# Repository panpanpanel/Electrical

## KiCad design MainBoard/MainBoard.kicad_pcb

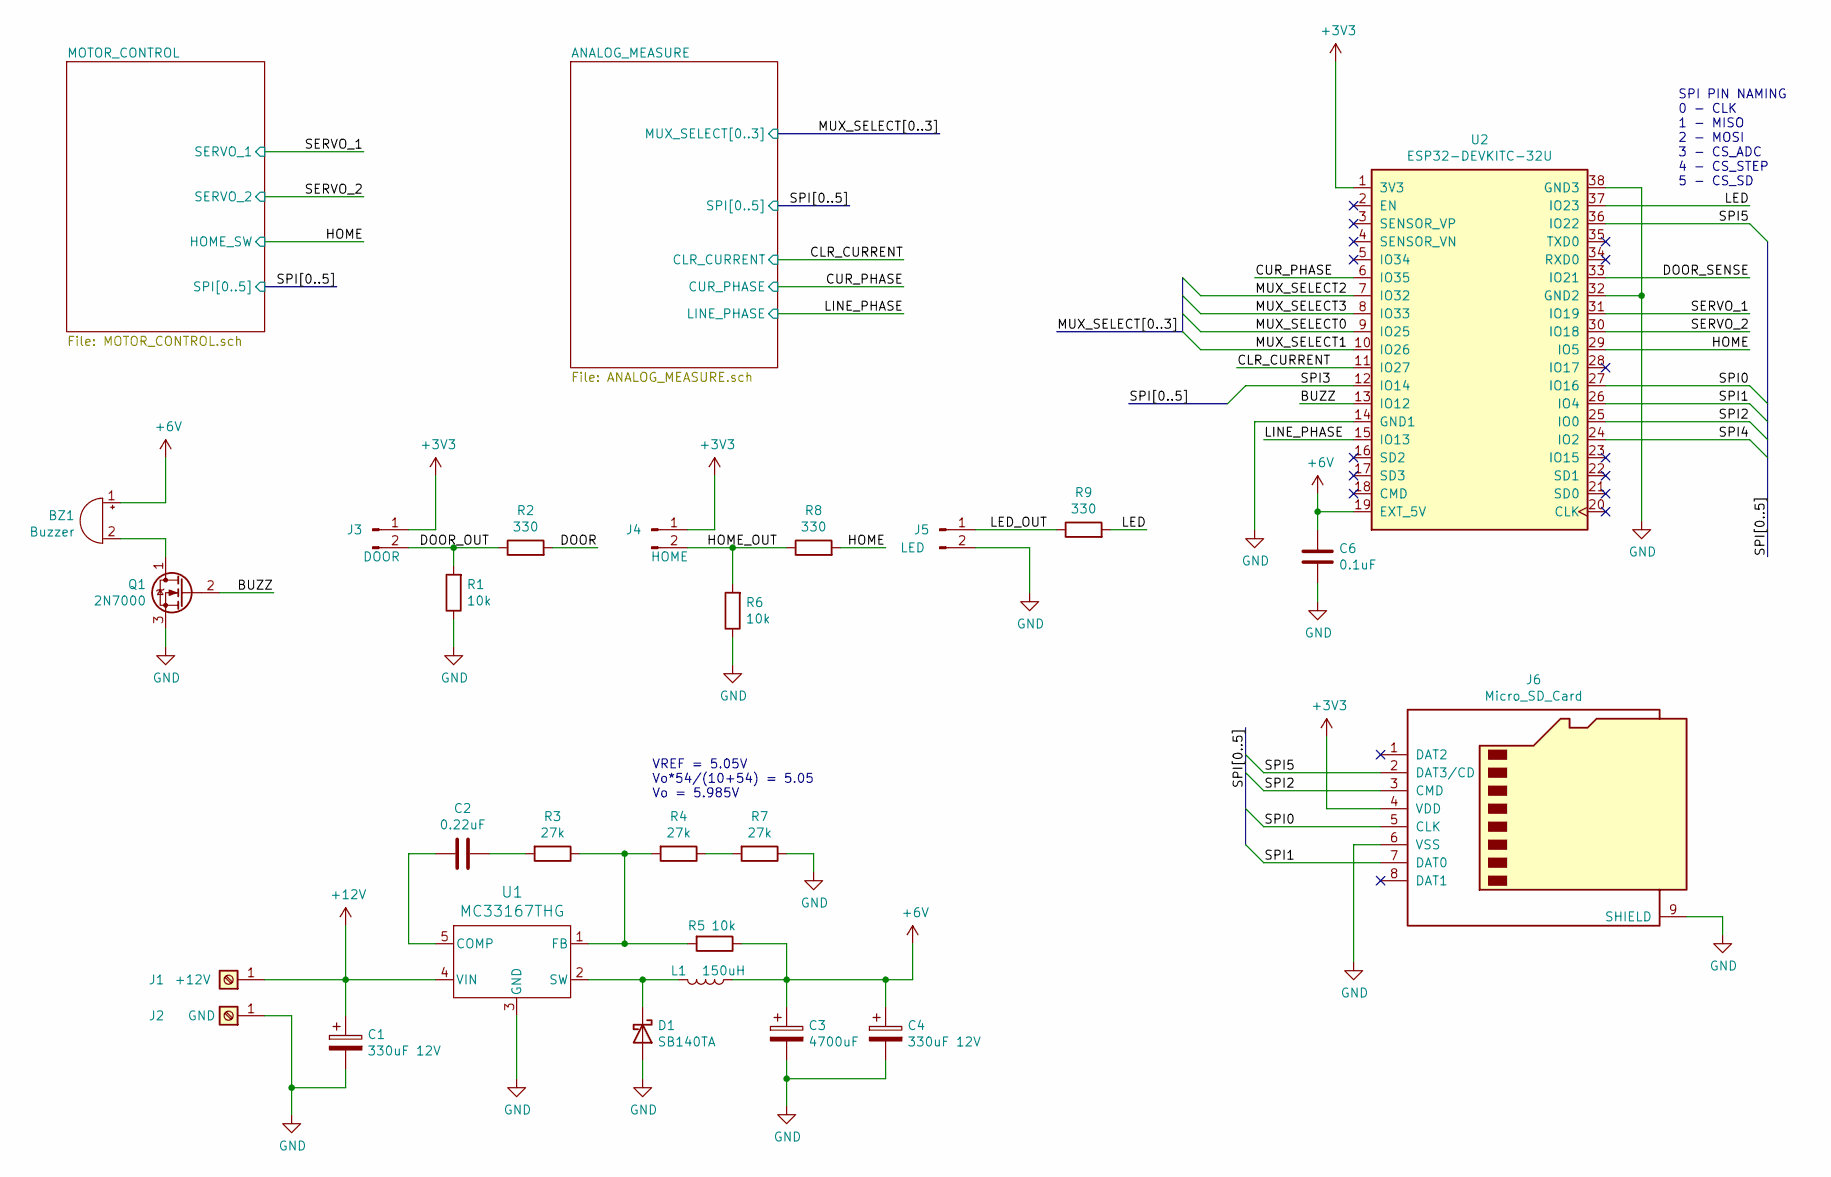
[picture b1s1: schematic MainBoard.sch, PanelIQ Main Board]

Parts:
BZ1: Buzzer; Buzzer_12x9.5RM7.6
C1, C4: 330uF 12V; CP_Radial_D8.0mm_P3.50mm
C2: 0.22uF; C_Rect_L4.0mm_W2.5mm_P2.50mm
C3: 4700uF; CP_Radial_D13.0mm_P5.00mm
C6: 0.1uF; C_Rect_L4.0mm_W2.5mm_P2.50mm
D1: SB140TA; D_DO-41_SOD81_P10.16mm_Horizontal
J1: +12V; Pin_D1.4mm_L8.5mm_W2.8mm_FlatFork
J2: GND; Pin_D1.4mm_L8.5mm_W2.8mm_FlatFork
J3: DOOR; PinHeader_1x02_P2.54mm_Vertical
J4: HOME; PinHeader_1x02_P2.54mm_Vertical
J5: LED; PinHeader_1x02_P2.54mm_Vertical
J6: Micro_SD_Card; microSD_HC_Wuerth_693072010801
L1: 150uH; L_Radial_D6.0mm_P4.00mm
Q1: 2N7000; TO-92_Inline
R1, R5, R6: 10k; R_Axial_DIN0204_L3.6mm_D1.6mm_P7.62mm_Horizontal
R2, R8, R9: 330; R_Axial_DIN0204_L3.6mm_D1.6mm_P7.62mm_Horizontal
R3, R4, R7: 27k; R_Axial_DIN0204_L3.6mm_D1.6mm_P7.62mm_Horizontal
U1: MC33167THG; TO-220-5_P3.4x3.8mm_StaggerOdd_Lead7.13mm_TabDown
U2: ESP32-DEVKITC-32U; MODULE_ESP32-DEVKITC-32U

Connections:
+6V: BZ1.1 (-), C3.1, C4.1, C6.1, L1.1, R5.1, U2.19 (EXT_5V); also elsewhere on the board
+12V: C1.1, J1.1, U1.4 (VIN); also elsewhere on the board
/BUZZ: Q1.2 (G), U2.13 (IO12)
/CLR_CURRENT: U2.11 (IO27); also elsewhere on the board
/CUR_PHASE: U2.6 (IO35); also elsewhere on the board
/DOOR: R2.2
/DOOR_OUT: J3.2, R1.2, R2.1
/DOOR_SENSE: U2.33 (IO21)
/HOME: R8.2, U2.29 (IO5); also elsewhere on the board
/HOME_OUT: J4.2, R6.2, R8.1
/LED: R9.2, U2.37 (IO23)
/LED_OUT: J5.1, R9.1
/LINE_PHASE: U2.15 (IO13); also elsewhere on the board
/MUX_SELECT0: U2.9 (IO25); also elsewhere on the board
/MUX_SELECT1: U2.10 (IO26); also elsewhere on the board
/MUX_SELECT2: U2.7 (IO32); also elsewhere on the board
/MUX_SELECT3: U2.8 (IO33); also elsewhere on the board
/SERVO_1: U2.31 (IO19); also elsewhere on the board
/SERVO_2: U2.30 (IO18); also elsewhere on the board
/SPI0: J6.5 (CLK), U2.27 (IO16); also elsewhere on the board
/SPI1: J6.7 (DAT0), U2.26 (IO4); also elsewhere on the board
/SPI2: J6.3 (CMD), U2.25 (IO0); also elsewhere on the board
/SPI3: U2.12 (IO14); also elsewhere on the board
/SPI4: U2.24 (IO2); also elsewhere on the board
/SPI5: J6.2 (DAT3/CD), U2.36 (IO22)
GND: C1.2, C3.2, C4.2, C6.2, D1.2 (A), J2.1, J5.2, J6.6 (VSS), J6.9 (SHIELD), Q1.3 (S), R1.1, R6.1, R7.1, U1.3 (GND), U2.14 (GND1), U2.32 (GND2), U2.38 (GND3); also elsewhere on the board
unnamed: BZ1.2 (+), Q1.1 (D)
unnamed: C2.1, U1.5 (COMP)
unnamed: C2.2, R3.2
unnamed: D1.1 (K), L1.2, U1.2 (SW)
unnamed: R3.1, R4.2, R5.2, U1.1 (FB)
unnamed: R4.1, R7.2

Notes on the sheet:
VREF = 5.05V Vo*54/(10+54) = 5.05 Vo = 5.985V
SPI PIN NAMING 0 - CLK 1 - MISO 2 - MOSI 3 - CS_ADC 4 - CS_STEP 5 - CS_SD

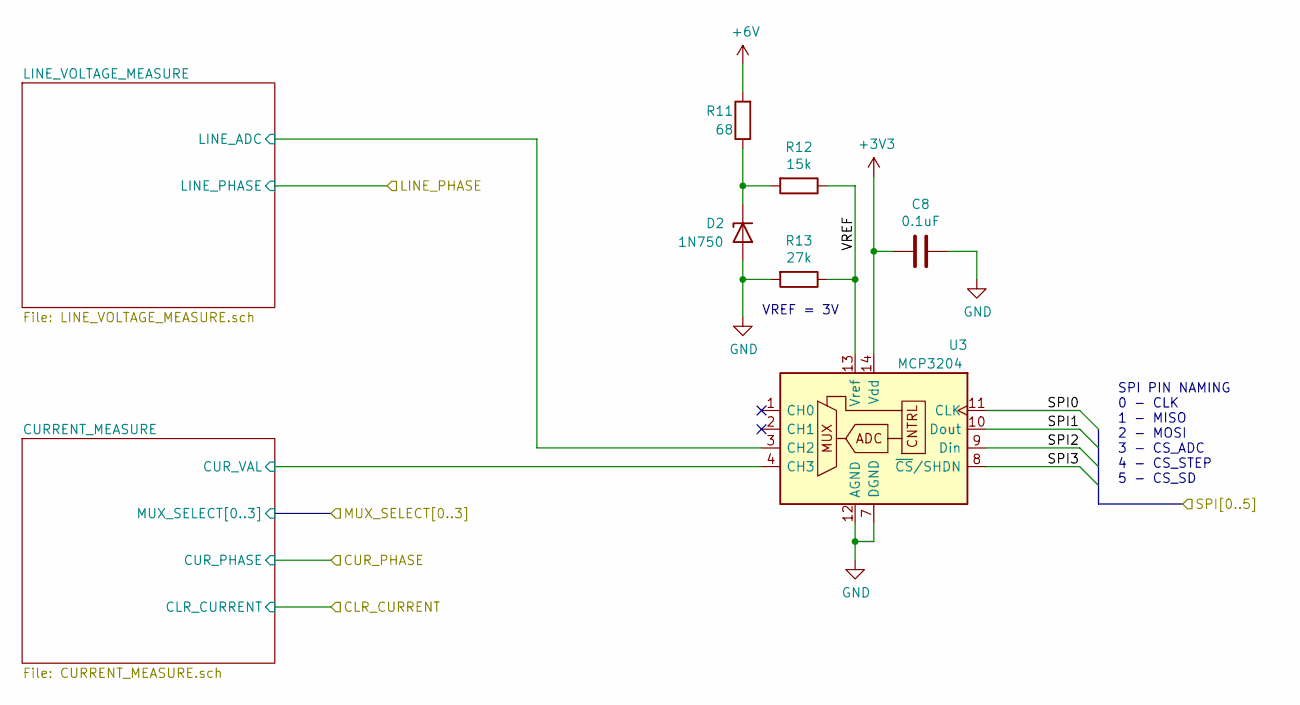
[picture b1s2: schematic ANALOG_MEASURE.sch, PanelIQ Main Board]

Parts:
C8: 0.1uF; C_Rect_L4.0mm_W2.5mm_P2.50mm
D2: 1N750; D_DO-35_SOD27_P10.16mm_Horizontal
R11: 68; R_Axial_DIN0204_L3.6mm_D1.6mm_P7.62mm_Horizontal
R12: 15k; R_Axial_DIN0204_L3.6mm_D1.6mm_P7.62mm_Horizontal
R13: 27k; R_Axial_DIN0204_L3.6mm_D1.6mm_P7.62mm_Horizontal
U3: MCP3204; DIP-14_W7.62mm_LongPads

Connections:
+6V: R11.2; also elsewhere on the board
/ANALOG_MEASURE/CURRENT_MEASURE/CUR_VAL: U3.4 (CH3); also elsewhere on the board
/ANALOG_MEASURE/LINE_VOLTAGE_MEASURE/LINE_ADC: U3.3 (CH2); also elsewhere on the board
/ANALOG_MEASURE/VREF: R12.1, R13.1, U3.13 (Vref)
/SPI0: U3.11 (CLK); also elsewhere on the board
/SPI1: U3.10 (Dout); also elsewhere on the board
/SPI2: U3.9 (Din); also elsewhere on the board
/SPI3: U3.8 (~CS~/SHDN); also elsewhere on the board
GND: C8.1, D2.2 (A), R13.2, U3.7 (DGND), U3.12 (AGND); also elsewhere on the board
unnamed: D2.1 (K), R11.1, R12.2

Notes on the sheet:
VREF = 3V
SPI PIN NAMING 0 - CLK 1 - MISO 2 - MOSI 3 - CS_ADC 4 - CS_STEP 5 - CS_SD

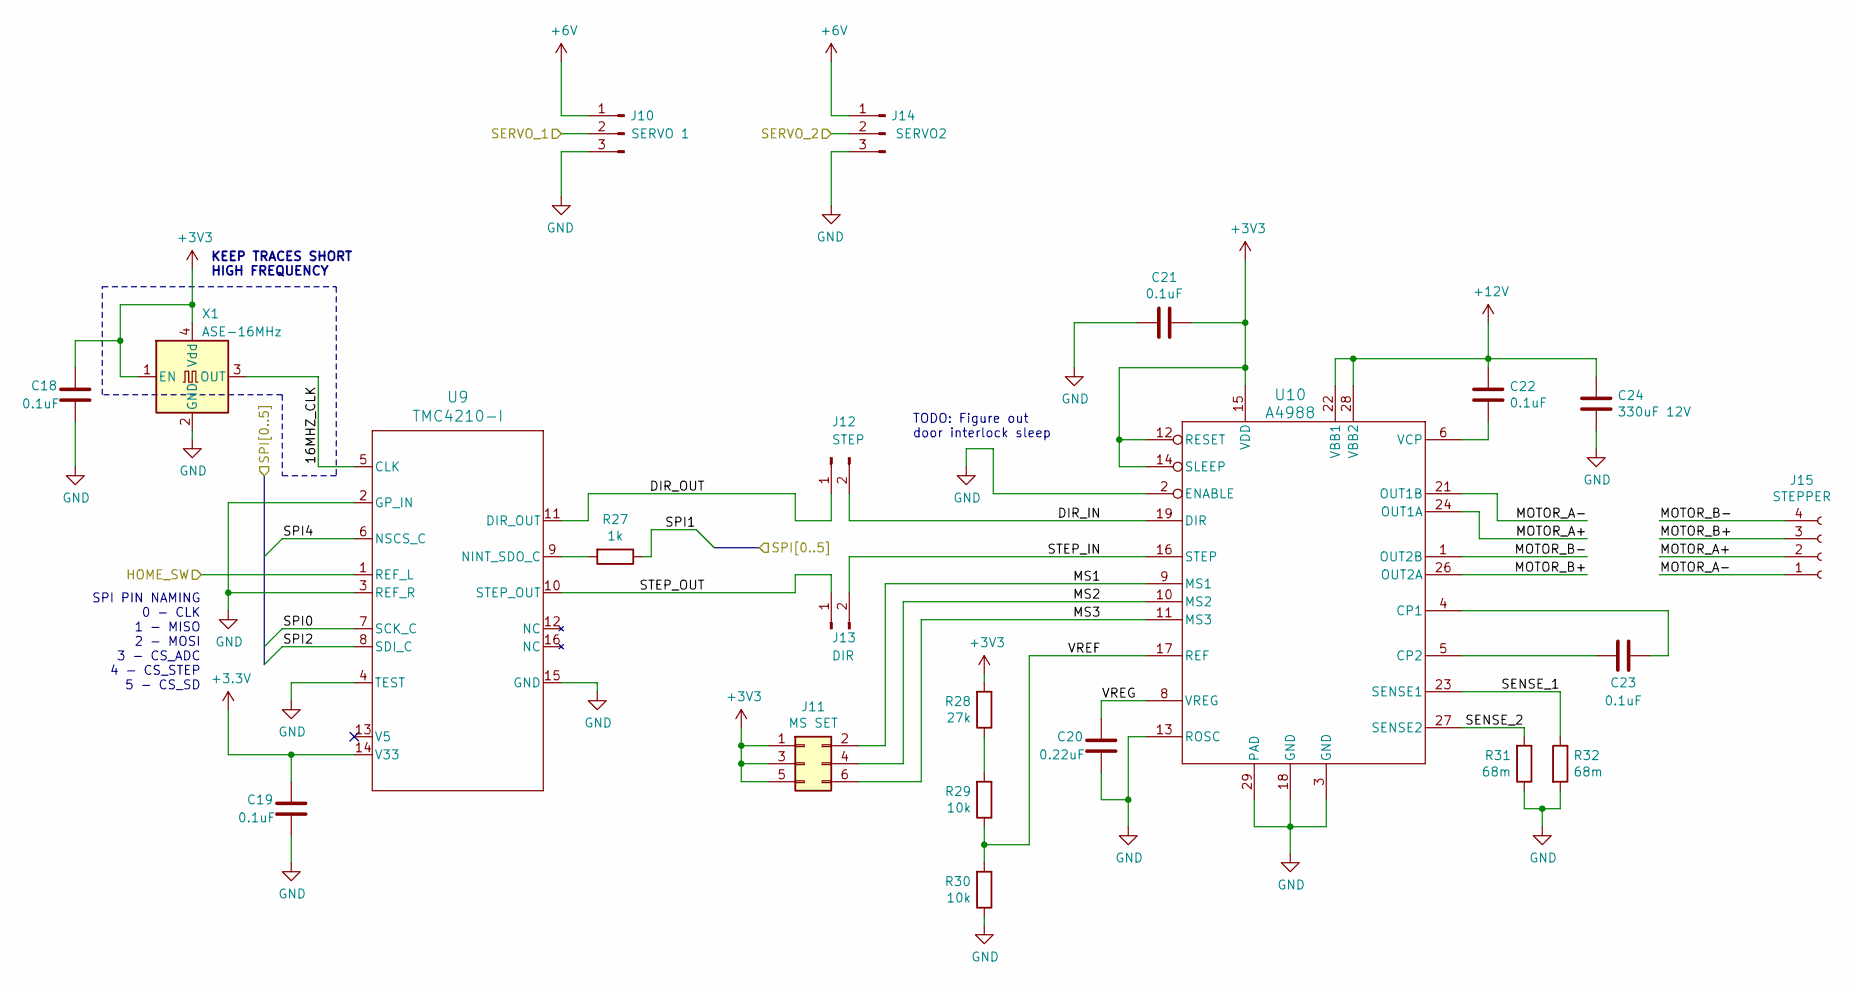
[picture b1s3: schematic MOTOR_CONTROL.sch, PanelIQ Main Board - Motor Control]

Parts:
C18, C19, C21, C22, C23: 0.1uF; C_Rect_L4.0mm_W2.5mm_P2.50mm
C20: 0.22uF; C_Rect_L4.0mm_W2.5mm_P2.50mm
C24: 330uF 12V; CP_Radial_D8.0mm_P3.50mm
J10: SERVO 1; PinHeader_1x03_P2.54mm_Vertical
J11: MS SET; PinHeader_2x03_P2.54mm_Vertical
J12: STEP; PinHeader_1x02_P2.54mm_Vertical
J13: DIR; PinHeader_1x02_P2.54mm_Vertical
J14: SERVO2; PinHeader_1x03_P2.54mm_Vertical
J15: STEPPER; JST_XH_B4B-XH-AM_1x04_P2.50mm_Vertical
R27: 1k; R_Axial_DIN0204_L3.6mm_D1.6mm_P7.62mm_Horizontal
R28: 27k; R_Axial_DIN0204_L3.6mm_D1.6mm_P7.62mm_Horizontal
R29, R30: 10k; R_Axial_DIN0204_L3.6mm_D1.6mm_P7.62mm_Horizontal
R31, R32: 68m; R_1206_3216Metric_Pad1.30x1.75mm_HandSolder
U9: TMC4210-I; SSOP-16_3.9x4.9mm_P0.635mm
U10: A4988; QFN-28-1EP_5x5mm_P0.5mm_EP3.35x3.35mm_ThermalVias
X1: ASE-16MHz; Oscillator_SMD_Abracon_ASE-4Pin_3.2x2.5mm

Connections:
+6V: J10.1, J14.1; also elsewhere on the board
+12V: C22.1, C24.1, U10.22 (VBB1), U10.28 (VBB2); also elsewhere on the board
/HOME: U9.1 (REF_L); also elsewhere on the board
/MOTOR_CONTROL/16MHZ_CLK: U9.5 (CLK), X1.3 (OUT)
/MOTOR_CONTROL/DIR_IN: J12.2, U10.19 (DIR)
/MOTOR_CONTROL/DIR_OUT: J12.1, U9.11 (DIR_OUT)
/MOTOR_CONTROL/MOTOR_A+: J15.2, U10.24 (OUT1A)
/MOTOR_CONTROL/MOTOR_A-: J15.1, U10.21 (OUT1B)
/MOTOR_CONTROL/MOTOR_B+: J15.3, U10.26 (OUT2A)
/MOTOR_CONTROL/MOTOR_B-: J15.4, U10.1 (OUT2B)
/MOTOR_CONTROL/MS1: J11.2, U10.9 (MS1)
/MOTOR_CONTROL/MS2: J11.4, U10.10 (MS2)
/MOTOR_CONTROL/MS3: J11.6, U10.11 (MS3)
/MOTOR_CONTROL/SENSE_1: R32.1, U10.23 (SENSE1)
/MOTOR_CONTROL/SENSE_2: R31.2, U10.27 (SENSE2)
/MOTOR_CONTROL/STEP_IN: J13.2, U10.16 (STEP)
/MOTOR_CONTROL/STEP_OUT: J13.1, U9.10 (STEP_OUT)
/MOTOR_CONTROL/VREF: R29.1, R30.2, U10.17 (REF)
/MOTOR_CONTROL/VREG: C20.1, U10.8 (VREG)
/SERVO_1: J10.2; also elsewhere on the board
/SERVO_2: J14.2; also elsewhere on the board
/SPI0: U9.7 (SCK_C); also elsewhere on the board
/SPI1: R27.1; also elsewhere on the board
/SPI2: U9.8 (SDI_C); also elsewhere on the board
/SPI4: U9.6 (NSCS_C); also elsewhere on the board
GND: C18.2, C19.2, C20.2, C21.2, C24.2, J10.3, J14.3, R30.1, R31.1, R32.2, U9.2 (GP_IN), U9.3 (REF_R), U9.4 (TEST), U9.15 (GND), U10.2 (ENABLE), U10.3 (GND), U10.13 (ROSC), U10.18 (GND), U10.29 (PAD), X1.2 (GND); also elsewhere on the board
unnamed: C22.2, U10.6 (VCP)
unnamed: C23.1, U10.4 (CP1)
unnamed: C23.2, U10.5 (CP2)
unnamed: R27.2, U9.9 (NINT_SDO_C)
unnamed: R28.1, R29.2

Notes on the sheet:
TODO: Figure out door interlock sleep
KEEP TRACES SHORT HIGH FREQUENCY
SPI PIN NAMING 0 - CLK 1 - MISO 2 - MOSI 3 - CS_ADC 4 - CS_STEP 5 - CS_SD

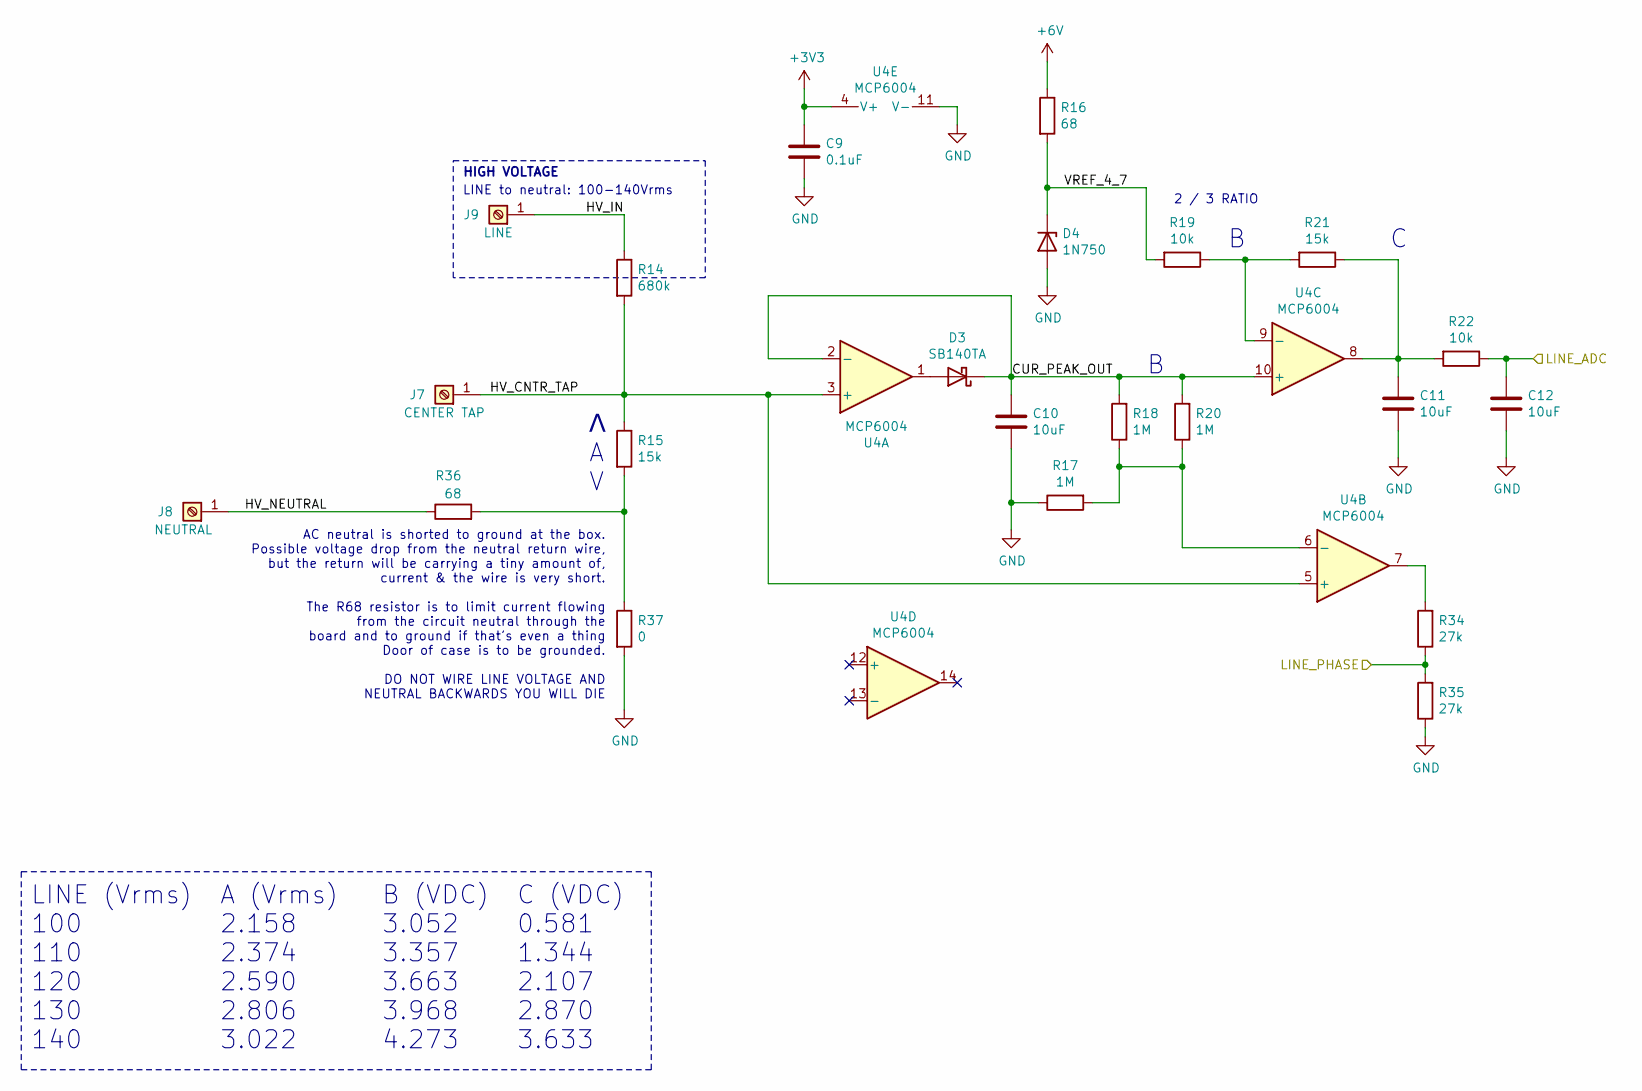
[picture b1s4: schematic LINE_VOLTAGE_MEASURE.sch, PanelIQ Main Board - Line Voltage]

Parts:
C9: 0.1uF; C_Rect_L4.0mm_W2.5mm_P2.50mm
C10, C11, C12: 10uF; CP_Radial_D5.0mm_P2.00mm
D3: SB140TA; D_DO-41_SOD81_P10.16mm_Horizontal
D4: 1N750; D_DO-35_SOD27_P10.16mm_Horizontal
J7: CENTER TAP; PinHeader_1x01_P2.54mm_Vertical
J8: NEUTRAL; PinHeader_1x01_P2.54mm_Vertical
J9: LINE; PinHeader_1x01_P2.54mm_Vertical
R14: 680k; R_Axial_DIN0207_L6.3mm_D2.5mm_P10.16mm_Horizontal
R15, R21: 15k; R_Axial_DIN0204_L3.6mm_D1.6mm_P7.62mm_Horizontal
R16, R36: 68; R_Axial_DIN0204_L3.6mm_D1.6mm_P7.62mm_Horizontal
R17, R18, R20: 1M; R_Axial_DIN0204_L3.6mm_D1.6mm_P7.62mm_Horizontal
R19, R22: 10k; R_Axial_DIN0204_L3.6mm_D1.6mm_P7.62mm_Horizontal
R34, R35: 27k; R_Axial_DIN0204_L3.6mm_D1.6mm_P7.62mm_Horizontal
R37: 0; R_Axial_DIN0204_L3.6mm_D1.6mm_P7.62mm_Horizontal
U4: MCP6004; DIP-14_W7.62mm_LongPads

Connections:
+6V: R16.1; also elsewhere on the board
/ANALOG_MEASURE/LINE_VOLTAGE_MEASURE/CUR_PEAK_OUT: C10.1, D3.1 (K), R18.2, R20.2, U4.2 (-), U4.10 (+)
/ANALOG_MEASURE/LINE_VOLTAGE_MEASURE/HV_CNTR_TAP: J7.1, R14.2, R15.1, U4.3 (+), U4.5 (+)
/ANALOG_MEASURE/LINE_VOLTAGE_MEASURE/HV_IN: J9.1, R14.1
/ANALOG_MEASURE/LINE_VOLTAGE_MEASURE/HV_NEUTRAL: J8.1, R36.1
/ANALOG_MEASURE/LINE_VOLTAGE_MEASURE/LINE_ADC: C12.1, R22.1; also elsewhere on the board
/ANALOG_MEASURE/LINE_VOLTAGE_MEASURE/VREF_4_7: D4.1 (K), R16.2, R19.2
/LINE_PHASE: R34.1, R35.2; also elsewhere on the board
GND: C9.2, C10.2, C11.2, C12.2, D4.2 (A), R17.1, R35.1, R37.2, U4.11 (V-); also elsewhere on the board
unnamed: C11.1, R21.1, R22.2, U4.8
unnamed: D3.2 (A), U4.1
unnamed: R15.2, R36.2, R37.1
unnamed: R17.2, R18.1, R20.1, U4.6 (-)
unnamed: R19.1, R21.2, U4.9 (-)
unnamed: R34.2, U4.7

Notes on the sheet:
LINE to neutral: 100-140Vrms
HIGH VOLTAGE
LINE (Vrms) 100 110 120 130 140
A (Vrms) 2.158 2.374 2.590 2.806 3.022
B (VDC) 3.052 3.357 3.663 3.968 4.273
C (VDC) 0.581 1.344 2.107 2.870 3.633
2 / 3 RATIO
Ʌ A V
AC neutral is shorted to ground at the box. Possible voltage drop from the neutral return wire, but the return will be carrying a tiny amount of, current & the wire is very short. The R68 resistor is to limit current flowing from the circuit neutral through the board and to ground if that's even a 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

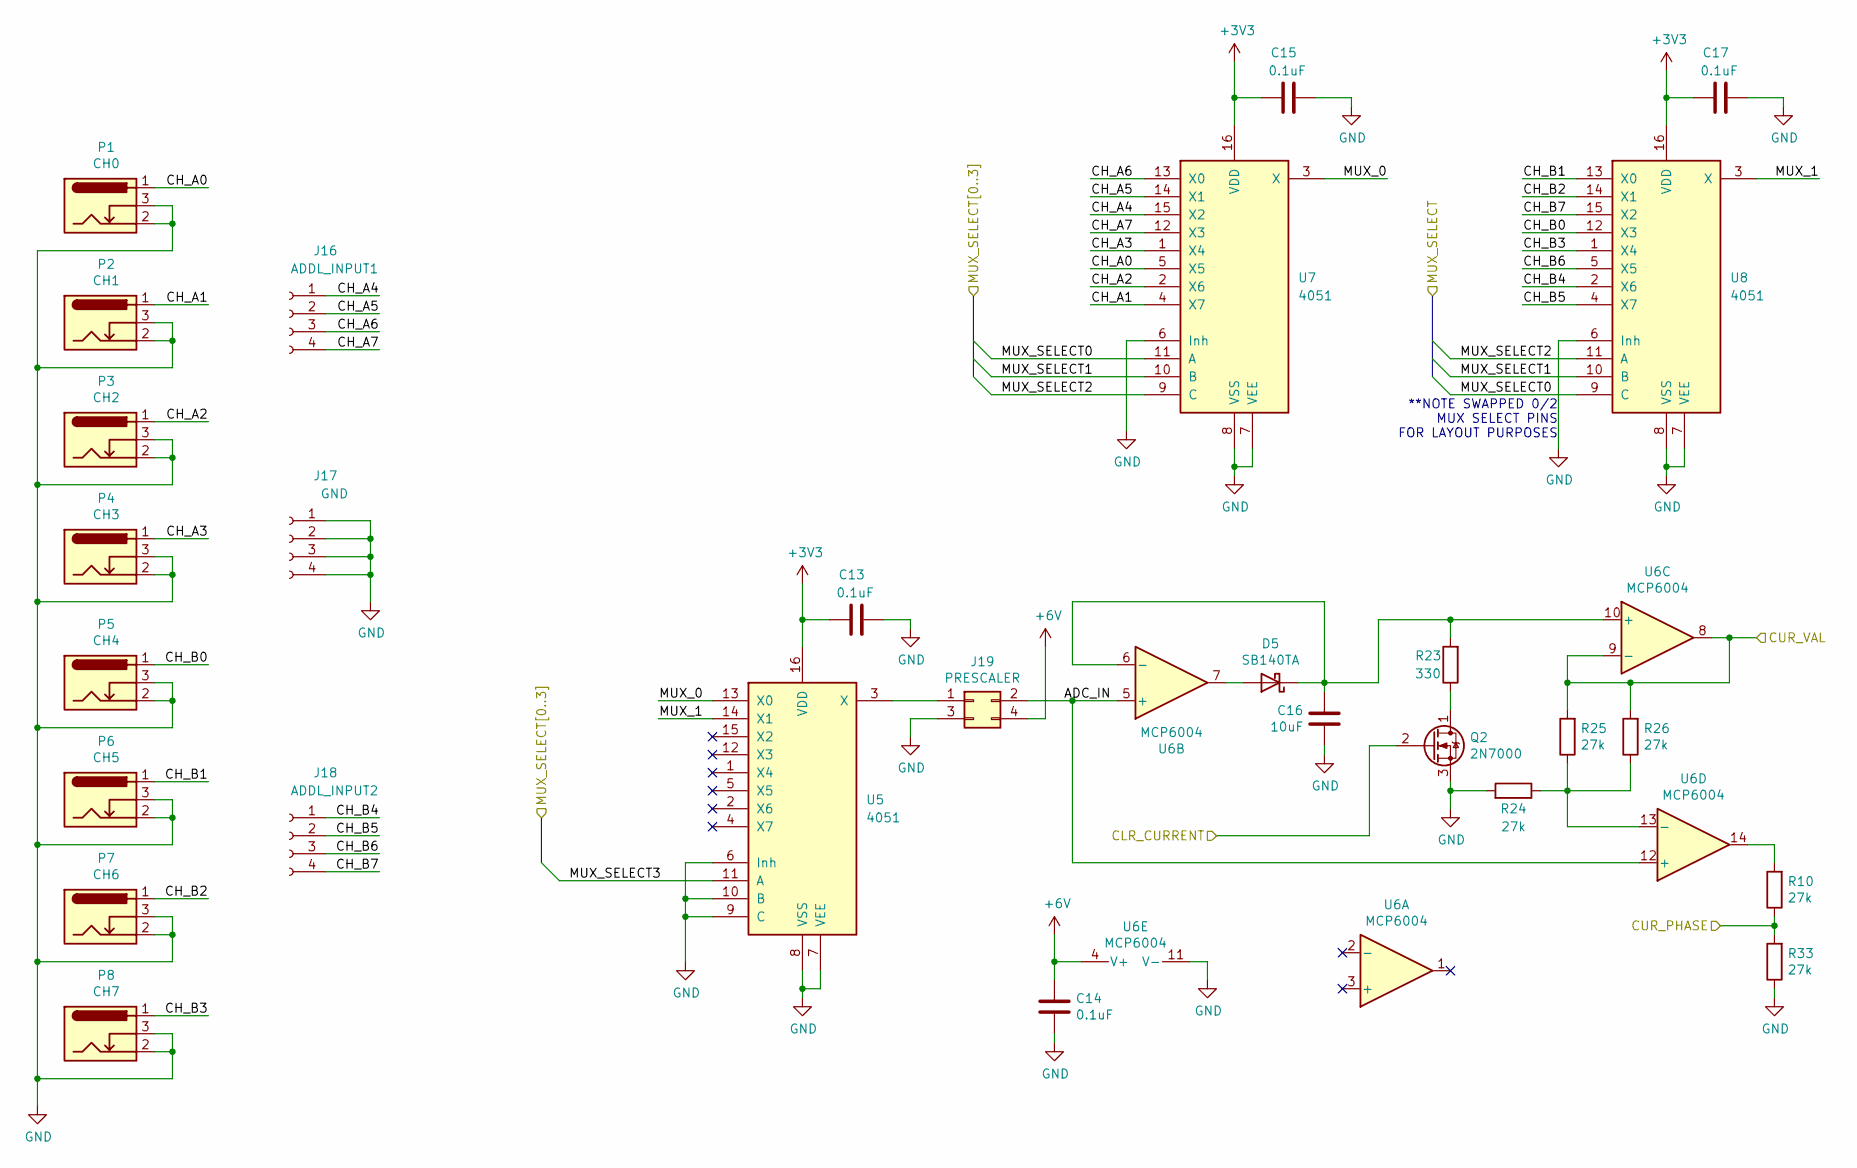
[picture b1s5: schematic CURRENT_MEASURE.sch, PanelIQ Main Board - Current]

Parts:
C13, C14, C15, C17: 0.1uF; C_Rect_L4.0mm_W2.5mm_P2.50mm
C16: 10uF; CP_Radial_D5.0mm_P2.00mm
D5: SB140TA; D_DO-41_SOD81_P10.16mm_Horizontal
J16: ADDL_INPUT1; PinHeader_1x04_P2.54mm_Vertical
J17: GND; PinHeader_1x04_P2.54mm_Vertical
J18: ADDL_INPUT2; PinHeader_1x04_P2.54mm_Vertical
J19: PRESCALER; PinHeader_2x02_P2.54mm_Vertical
P1: CH0; DC-005
P2: CH1; DC-005
P3: CH2; DC-005
P4: CH3; DC-005
P5: CH4; DC-005
P6: CH5; DC-005
P7: CH6; DC-005
P8: CH7; DC-005
Q2: 2N7000; TO-92_Inline
R10, R24, R25, R26, R33: 27k; R_Axial_DIN0204_L3.6mm_D1.6mm_P7.62mm_Horizontal
R23: 330; R_Axial_DIN0204_L3.6mm_D1.6mm_P7.62mm_Horizontal
U5, U7, U8: 4051; DIP-16_W7.62mm_LongPads
U6: MCP6004; DIP-14_W7.62mm_LongPads

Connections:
+6V: C14.1, J19.4, U6.4 (V+); also elsewhere on the board
/ANALOG_MEASURE/CURRENT_MEASURE/ADC_IN: J19.2, U6.5 (+), U6.12 (+)
/ANALOG_MEASURE/CURRENT_MEASURE/CH_A0: P1.1, U7.5 (X5)
/ANALOG_MEASURE/CURRENT_MEASURE/CH_A1: P2.1, U7.4 (X7)
/ANALOG_MEASURE/CURRENT_MEASURE/CH_A2: P3.1, U7.2 (X6)
/ANALOG_MEASURE/CURRENT_MEASURE/CH_A3: P4.1, U7.1 (X4)
/ANALOG_MEASURE/CURRENT_MEASURE/CH_A4: J16.1, U7.15 (X2)
/ANALOG_MEASURE/CURRENT_MEASURE/CH_A5: J16.2, U7.14 (X1)
/ANALOG_MEASURE/CURRENT_MEASURE/CH_A6: J16.3, U7.13 (X0)
/ANALOG_MEASURE/CURRENT_MEASURE/CH_A7: J16.4, U7.12 (X3)
/ANALOG_MEASURE/CURRENT_MEASURE/CH_B0: P5.1, U8.12 (X3)
/ANALOG_MEASURE/CURRENT_MEASURE/CH_B1: P6.1, U8.13 (X0)
/ANALOG_MEASURE/CURRENT_MEASURE/CH_B2: P7.1, U8.14 (X1)
/ANALOG_MEASURE/CURRENT_MEASURE/CH_B3: P8.1, U8.1 (X4)
/ANALOG_MEASURE/CURRENT_MEASURE/CH_B4: J18.1, U8.2 (X6)
/ANALOG_MEASURE/CURRENT_MEASURE/CH_B5: J18.2, U8.4 (X7)
/ANALOG_MEASURE/CURRENT_MEASURE/CH_B6: J18.3, U8.5 (X5)
/ANALOG_MEASURE/CURRENT_MEASURE/CH_B7: J18.4, U8.15 (X2)
/ANALOG_MEASURE/CURRENT_MEASURE/CUR_VAL: R25.2, R26.2, U6.8, U6.9 (-); also elsewhere on the board
/ANALOG_MEASURE/CURRENT_MEASURE/MUX_0: U5.13 (X0), U7.3 (X)
/ANALOG_MEASURE/CURRENT_MEASURE/MUX_1: U5.14 (X1), U8.3 (X)
/CLR_CURRENT: Q2.2 (G); also elsewhere on the board
/CUR_PHASE: R10.1, R33.2; also elsewhere on the board
/MUX_SELECT0: U7.11 (A), U8.9 (C); also elsewhere on the board
/MUX_SELECT1: U7.10 (B), U8.10 (B); also elsewhere on the board
/MUX_SELECT2: U7.9 (C), U8.11 (A); also elsewhere on the board
/MUX_SELECT3: U5.11 (A); also elsewhere on the board
GND: C13.2, C14.2, C15.2, C16.1, C17.2, J17.1, J17.2, J17.3, J17.4, J19.3, P1.2, P1.3, P2.2, P2.3, P3.2, P3.3, P4.2, P4.3, P5.2, P5.3, P6.2, P6.3, P7.2, P7.3, P8.2, P8.3, Q2.3 (S), R24.2, R33.1, U5.6 (Inh), U5.7 (VEE), U5.8 (VSS), U5.9 (C), U5.10 (B), U6.11 (V-), U7.6 (Inh), U7.7 (VEE), U7.8 (VSS), U8.6 (Inh), U8.7 (VEE), U8.8 (VSS); also elsewhere on the board
unnamed: C16.2, D5.1 (K), R23.2, U6.6 (-), U6.10 (+)
unnamed: D5.2 (A), U6.7
unnamed: J19.1, U5.3 (X)
unnamed: Q2.1 (D), R23.1
unnamed: R10.2, U6.14
unnamed: R24.1, R25.1, R26.1, U6.13 (-)

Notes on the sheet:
**NOTE SWAPPED 0/2 MUX SELECT PINS FOR LAYOUT PURPOSES

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
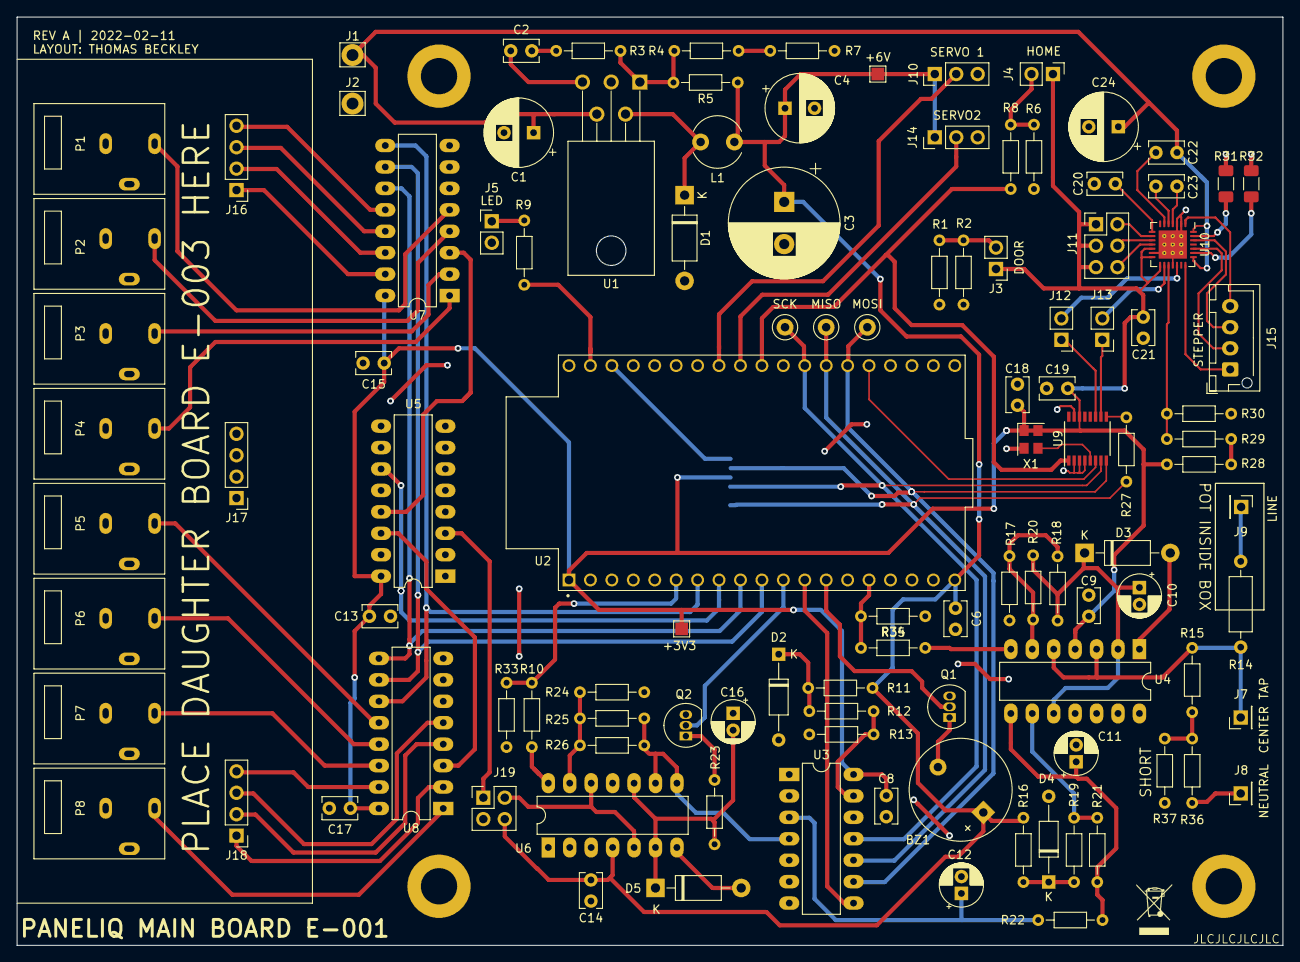
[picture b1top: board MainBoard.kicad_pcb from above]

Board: 2 copper layers, 150.0 x 110.0 mm, 111 parts (1 on the bottom side), 92 nets.

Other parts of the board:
+3V3, +6V: TestPoint_Pad_1.5x1.5mm
MISO: TestPoint_Loop_D2.50mm_Drill1.0mm
MOSI: TestPoint_Loop_D2.50mm_Drill1.0mm
SCK: TestPoint_Loop_D2.50mm_Drill1.0mm

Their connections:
+6V: +6V.1; also elsewhere on the board
/SPI0: SCK.1; also elsewhere on the board
/SPI1: MISO.1; also elsewhere on the board
/SPI2: MOSI.1; also elsewhere on the board

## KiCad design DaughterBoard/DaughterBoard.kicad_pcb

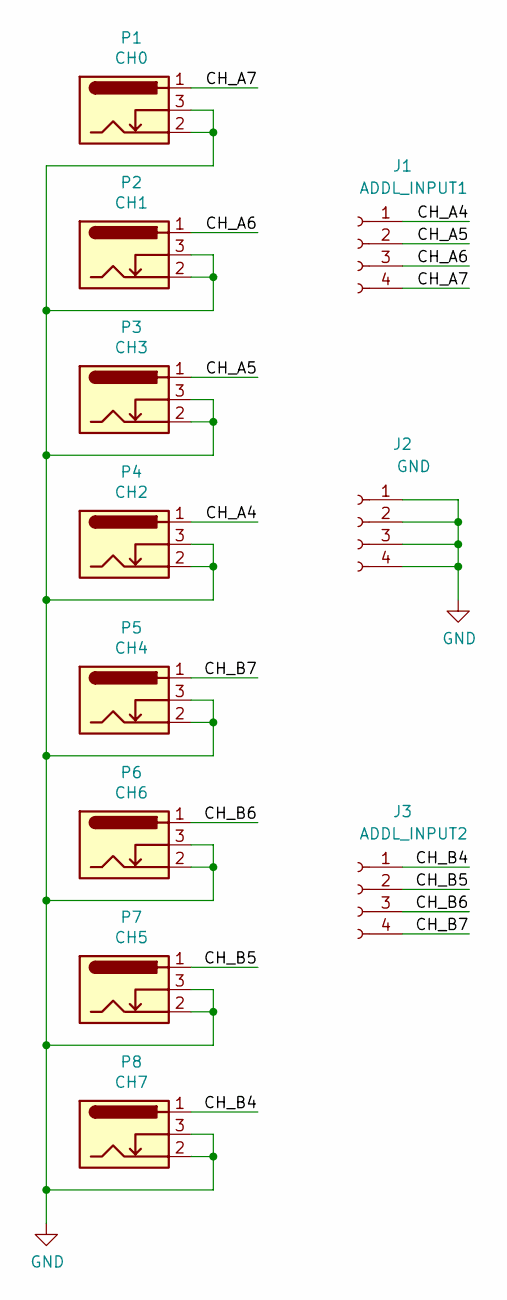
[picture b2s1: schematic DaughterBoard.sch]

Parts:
J1: ADDL_INPUT1; PinHeader_1x04_P2.54mm_Vertical
J2: GND; PinHeader_1x04_P2.54mm_Vertical
J3: ADDL_INPUT2; PinHeader_1x04_P2.54mm_Vertical
P1: CH0; DC-005
P2: CH1; DC-005
P3: CH3; DC-005
P4: CH2; DC-005
P5: CH4; DC-005
P6: CH6; DC-005
P7: CH5; DC-005
P8: CH7; DC-005

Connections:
/CH_A4: J1.1, P4.1
/CH_A5: J1.2, P3.1
/CH_A6: J1.3, P2.1
/CH_A7: J1.4, P1.1
/CH_B4: J3.1, P8.1
/CH_B5: J3.2, P7.1
/CH_B6: J3.3, P6.1
/CH_B7: J3.4, P5.1
GND: J2.1, J2.2, J2.3, J2.4, P1.2, P1.3, P2.2, P2.3, P3.2, P3.3, P4.2, P4.3, P5.2, P5.3, P6.2, P6.3, P7.2, P7.3, P8.2, P8.3

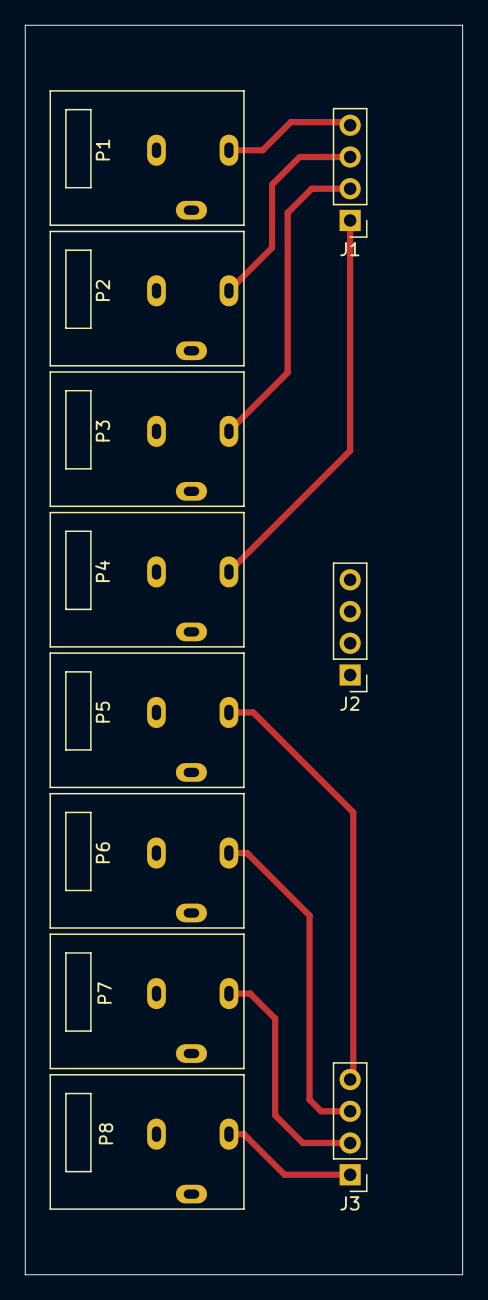
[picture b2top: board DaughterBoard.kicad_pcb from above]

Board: 2 copper layers, 35.0 x 100.0 mm, 11 parts (0 on the bottom side), 9 nets.

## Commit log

2021-12-07 PRELIM E-001 release
2022-01-30 Catchup Commit
2022-01-31 R0.1
2022-02-10 Layout Main Board
    Layout main PCB
2022-02-10 Add Daughter Board
2022-02-10 Update Voltage calculation
2022-02-10 Update Voltage Divider
2022-02-12 Final MainBoard
2022-03-18 E-005-Electrical-Block-Diagram.drawio
2022-03-18 Added E-006-DUT-Calibration-Wiring-Diagram.drawio
